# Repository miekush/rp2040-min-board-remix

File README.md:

# RP2040 Minimum System Design
A remix of the RP2040 Minimum System Design with some added features

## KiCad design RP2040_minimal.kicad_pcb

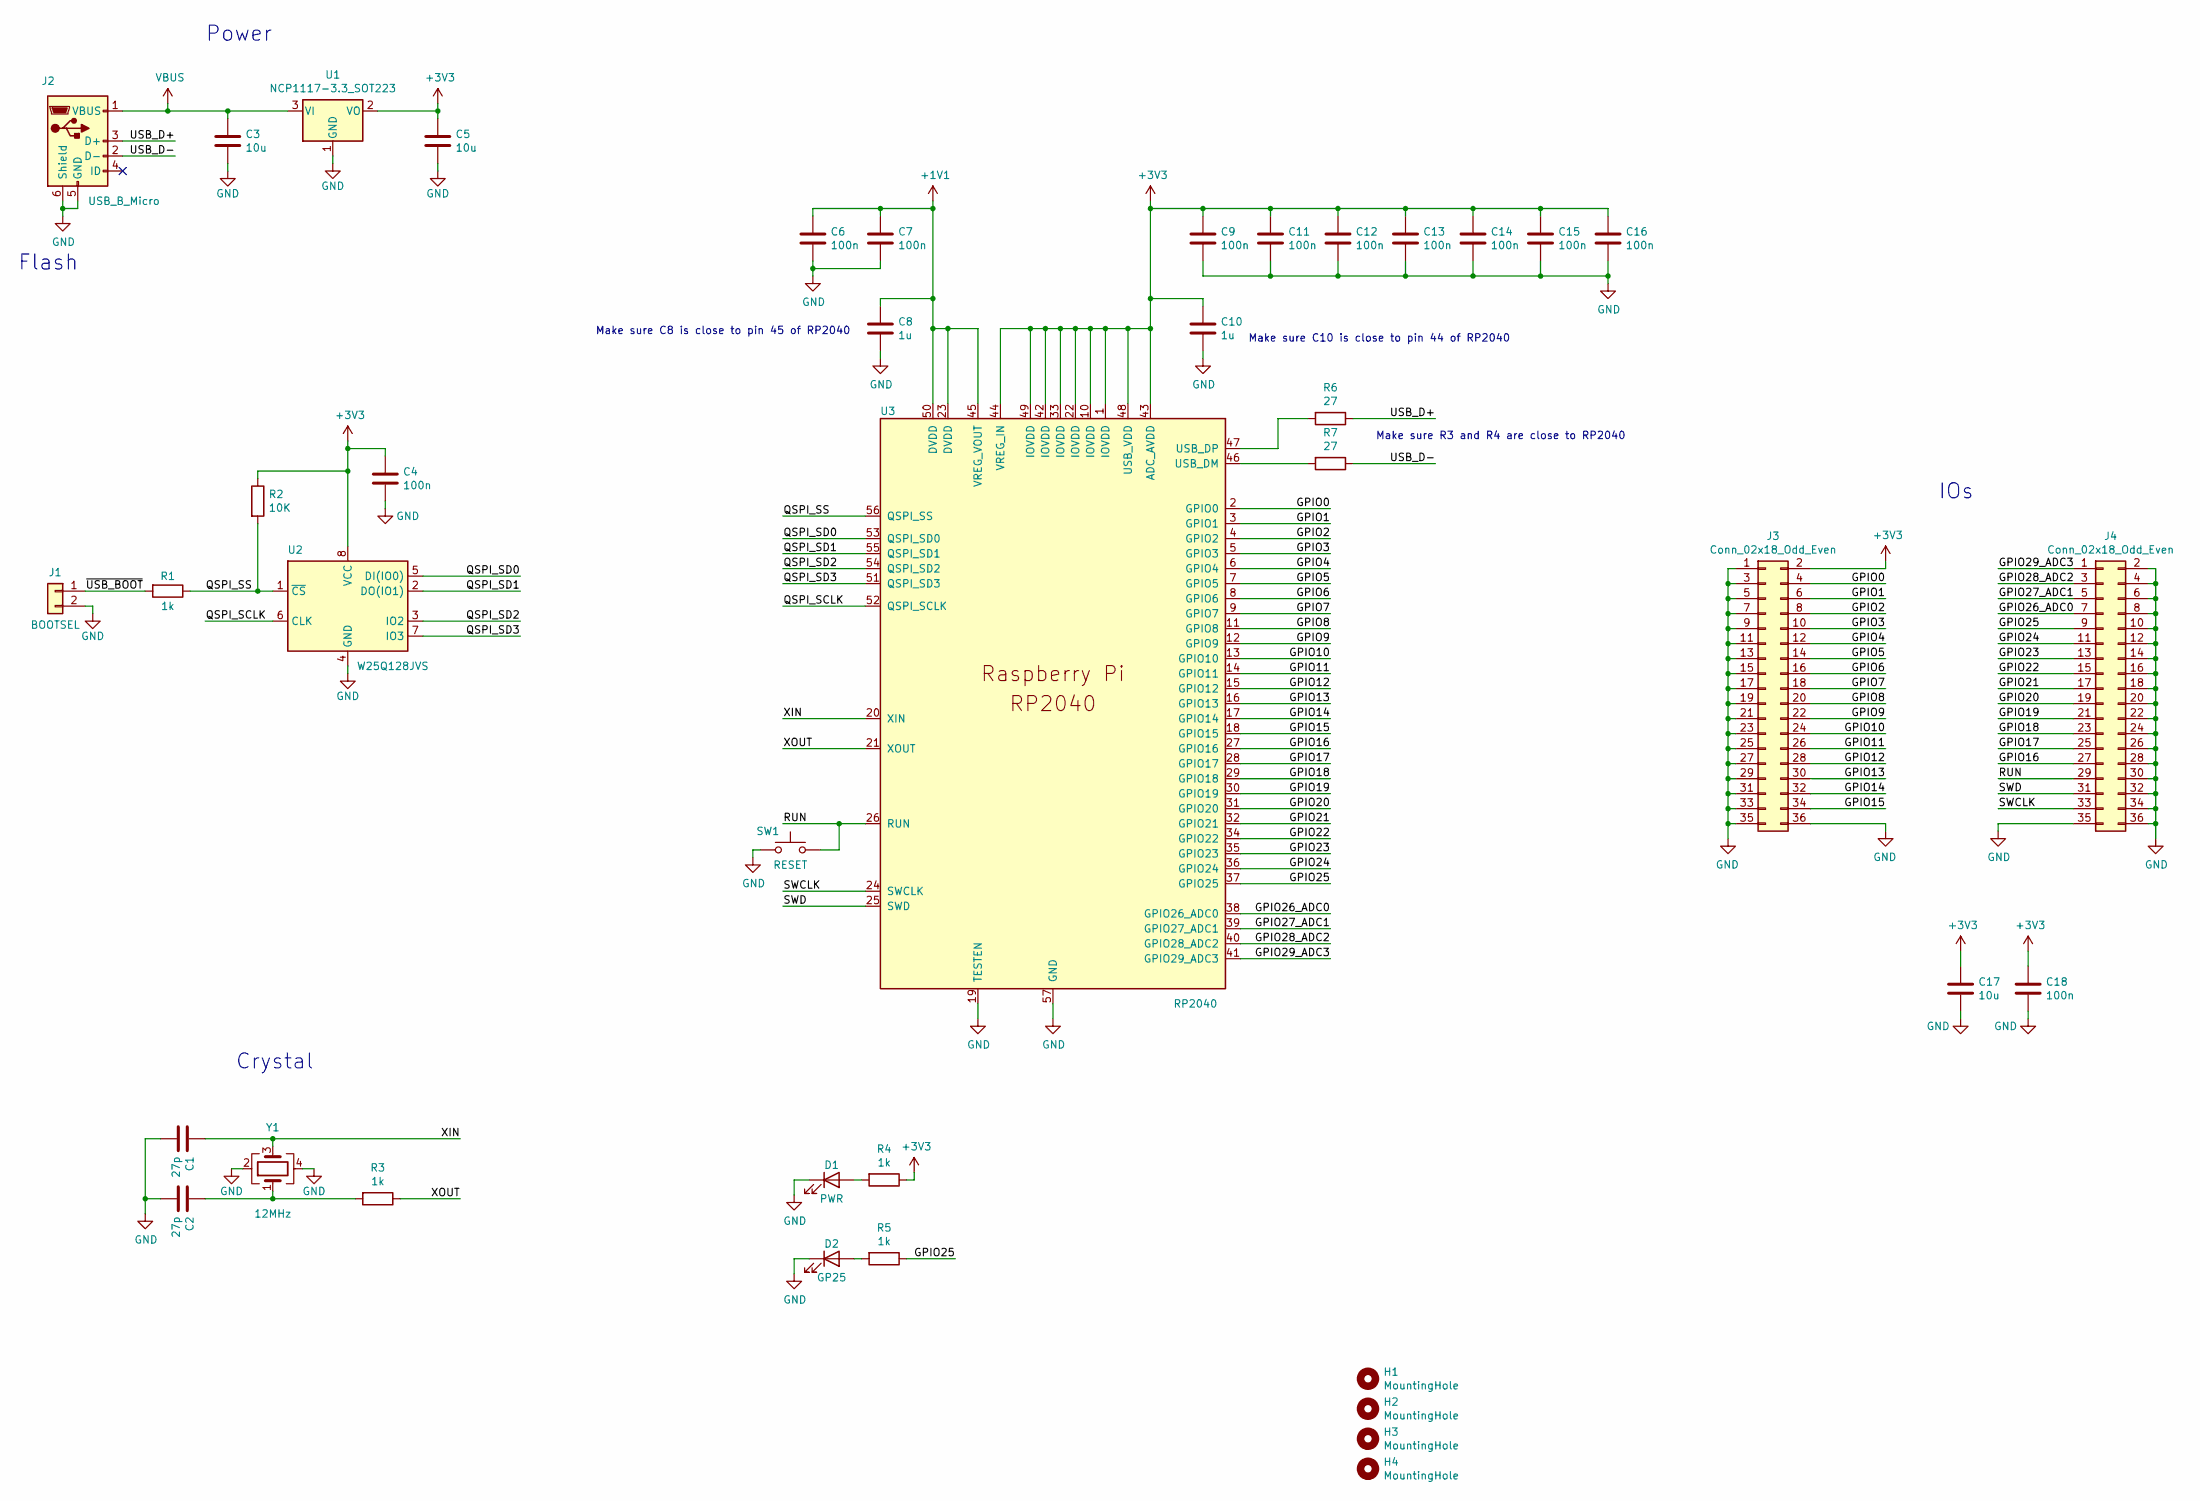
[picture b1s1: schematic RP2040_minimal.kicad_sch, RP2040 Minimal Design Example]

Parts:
C1, C2: 27p; C_0603_1608Metric
C3, C5, C17: 10u; C_0805_2012Metric
C4, C6, C7, C9, C11, C12, C13, C14, C15, C16, C18: 100n; C_0603_1608Metric
C8, C10: 1u; C_0603_1608Metric
D1: PWR; LED_0603_1608Metric
D2: GP25; LED_0603_1608Metric
H1, H2, H3, H4: MountingHole; MountingHole_2.7mm_M2.5
J1: BOOTSEL; PinHeader_1x02_P2.54mm_Vertical
J2: USB_B_Micro; USB_Micro-B_Amphenol_10103594-0001LF_Horizontal_modified
J3, J4: Conn_02x18_Odd_Even; PinHeader_2x18_P2.54mm_Vertical
R1, R3, R4, R5: 1k; R_0603_1608Metric
R2: 10K; R_0603_1608Metric
R6, R7: 27; R_0603_1608Metric
SW1: RESET; SW_PUSH_6mm
U1: NCP1117-3.3_SOT223; SOT-223-3_TabPin2
U2: W25Q128JVS; SOIC-8_5.23x5.23mm_P1.27mm
U3: RP2040; RP2040-QFN-56
Y1: 12MHz; Crystal_SMD_Abracon_ABM8G-4Pin_3.2x2.5mm

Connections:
+1V1: C6.1, C7.1, C8.1, U3.23 (DVDD), U3.45 (VREG_VOUT), U3.50 (DVDD)
+3V3: C4.1, C5.1, C9.1, C10.1, C11.1, C12.1, C13.1, C14.1, C15.1, C16.1, C17.1, C18.1, J3.2, R2.1, R4.1, U1.2 (VO), U2.8 (VCC), U3.1 (IOVDD), U3.10 (IOVDD), U3.22 (IOVDD), U3.33 (IOVDD), U3.42 (IOVDD), U3.43 (ADC_AVDD), U3.44 (VREG_IN), U3.48 (USB_VDD), U3.49 (IOVDD)
/GPIO0: J3.4, U3.2 (GPIO0)
/GPIO1: J3.6, U3.3 (GPIO1)
/GPIO2: J3.8, U3.4 (GPIO2)
/GPIO3: J3.10, U3.5 (GPIO3)
/GPIO4: J3.12, U3.6 (GPIO4)
/GPIO5: J3.14, U3.7 (GPIO5)
/GPIO6: J3.16, U3.8 (GPIO6)
/GPIO7: J3.18, U3.9 (GPIO7)
/GPIO8: J3.20, U3.11 (GPIO8)
/GPIO9: J3.22, U3.12 (GPIO9)
/GPIO10: J3.24, U3.13 (GPIO10)
/GPIO11: J3.26, U3.14 (GPIO11)
/GPIO12: J3.28, U3.15 (GPIO12)
/GPIO13: J3.30, U3.16 (GPIO13)
/GPIO14: J3.32, U3.17 (GPIO14)
/GPIO15: J3.34, U3.18 (GPIO15)
/GPIO16: J4.27, U3.27 (GPIO16)
/GPIO17: J4.25, U3.28 (GPIO17)
/GPIO18: J4.23, U3.29 (GPIO18)
/GPIO19: J4.21, U3.30 (GPIO19)
/GPIO20: J4.19, U3.31 (GPIO20)
/GPIO21: J4.17, U3.32 (GPIO21)
/GPIO22: J4.15, U3.34 (GPIO22)
/GPIO23: J4.13, U3.35 (GPIO23)
/GPIO24: J4.11, U3.36 (GPIO24)
/GPIO25: J4.9, R5.1, U3.37 (GPIO25)
/GPIO26_ADC0: J4.7, U3.38 (GPIO26_ADC0)
/GPIO27_ADC1: J4.5, U3.39 (GPIO27_ADC1)
/GPIO28_ADC2: J4.3, U3.40 (GPIO28_ADC2)
/GPIO29_ADC3: J4.1, U3.41 (GPIO29_ADC3)
/QSPI_SCLK: U2.6 (CLK), U3.52 (QSPI_SCLK)
/QSPI_SD0: U2.5 (DI(IO0)), U3.53 (QSPI_SD0)
/QSPI_SD1: U2.2 (DO(IO1)), U3.55 (QSPI_SD1)
/QSPI_SD2: U2.3 (IO2), U3.54 (QSPI_SD2)
/QSPI_SD3: U2.7 (IO3), U3.51 (QSPI_SD3)
/QSPI_SS: R1.1, R2.2, U2.1 (~CS), U3.56 (QSPI_SS)
/RUN: J4.29, SW1.2, U3.26 (RUN)
/SWCLK: J4.33, U3.24 (SWCLK)
/SWD: J4.31, U3.25 (SWD)
/USB_D+: J2.3 (D+), R6.1
/USB_D-: J2.2 (D-), R7.1
/XIN: C1.1, U3.20 (XIN), Y1.3
/XOUT: R3.1, U3.21 (XOUT)
/~USB_BOOT: J1.1, R1.2
GND: C1.2, C2.2, C3.2, C4.2, C5.2, C6.2, C7.2, C8.2, C9.2, C10.2, C11.2, C12.2, C13.2, C14.2, C15.2, C16.2, C17.2, C18.2, D1.1 (K), D2.1 (K), J1.2, J2.5 (GND), J2.6 (Shield), J3.1, J3.3, J3.5, J3.7, J3.9, J3.11, J3.13, J3.15, J3.17, J3.19, J3.21, J3.23, J3.25, J3.27, J3.29, J3.31, J3.33, J3.35, J3.36, J4.2, J4.4, J4.6, J4.8, J4.10, J4.12, J4.14, J4.16, J4.18, J4.20, J4.22, J4.24, J4.26, J4.28, J4.30, J4.32, J4.34, J4.35, J4.36, SW1.1, U1.1 (GND), U2.4 (GND), U3.19 (TESTEN), U3.57 (GND), Y1.2, Y1.4
unnamed: C2.1, R3.2, Y1.1
unnamed: D1.2 (A), R4.2
unnamed: D2.2 (A), R5.2
unnamed: R6.2, U3.47 (USB_DP)
unnamed: R7.2, U3.46 (USB_DM)
VBUS: C3.1, J2.1 (VBUS), U1.3 (VI)

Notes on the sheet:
Make sure C10 is close to pin 44 of RP2040
Power
Crystal
IOs
Make sure C8 is close to pin 45 of RP2040
Flash
Make sure R3 and R4 are close to RP2040

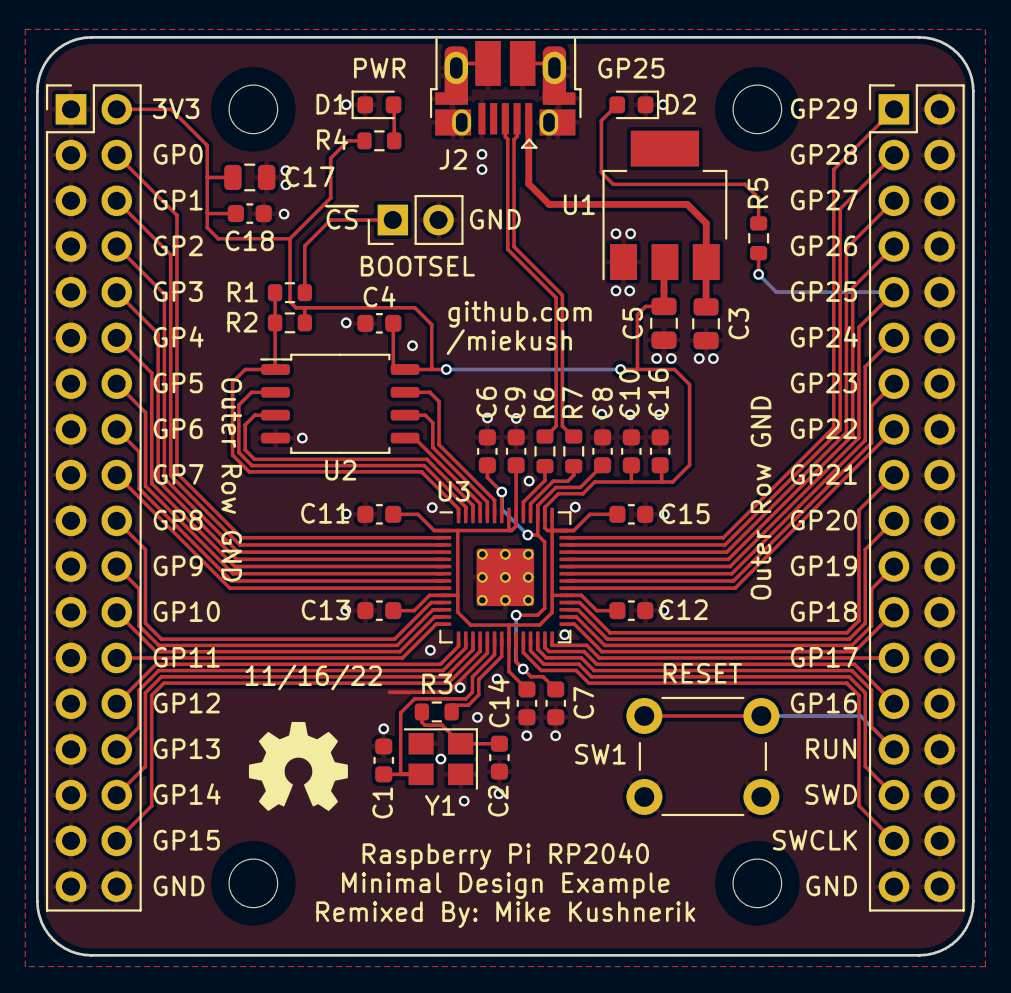
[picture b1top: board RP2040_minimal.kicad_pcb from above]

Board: 2 copper layers, 52.0 x 51.0 mm, 40 parts (0 on the bottom side), 53 nets.

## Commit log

2023-02-23 Initial upload
